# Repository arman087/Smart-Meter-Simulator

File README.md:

# Smart Meter Simulator

Portable lab board that **acts like a Dutch/Belgian DSMR smart meter P1 port**.  
Park it on battery in a building corner, plug in [P1 Ghost](https://github.com/arman087/P1_ghost), and test Ghost Wi‑Fi range without a real meter.

| This board (meter) | P1 Ghost / OSM (reader) |
|--------------------|-------------------------|
| Female RJ12 | Male RJ12 |
| **Supplies** +5 V on pin 1 | Takes +5 V |
| **Senses** Data Request on pin 2 | Drives Request high |
| **Open-collector / opto** Data on pin 5 | Reads Data |

**MCU:** ESP32-C3-MINI-1 (Wi‑Fi on for config / OTA) · **P1 serial:** 115200 8N1 inverted open-drain  
**Telegram store:** microSD · **Build volume:** ~5 boards (JLCPCB)

**Why / how:** **[DESIGN_REPORT.md](DESIGN_REPORT.md)** · **Firmware:** **[FIRMWARE_GUIDE.md](FIRMWARE_GUIDE.md)** · **Pause / next:** **[NEXT_STEPS.md](NEXT_STEPS.md)** · **KiCad:** `my_design/Slimme_meter_Sim/`

---

## Progress (schematic + PCB — Aug 2026)

| Block | Status |
|-------|--------|
| USB-C → bq25185 → TPS61023 → **SYS_5V** | Drawn (`SCH_1_USB_5volt_sch`) |
| **TPS26625** eFuse → `P1_5V`, caps, green power LED, test points, RJ12 | Drawn |
| **SY8088** buck → **VCC_3V3** | Drawn |
| **ESP32-C3-MINI-1** on 3V3; EN RC; GPIO2/8 pull-ups; USB = GPIO18/19 | Drawn |
| RGB on GPIO10; Schottky-fed LED supply | Drawn |
| **6N137S** Data TX (GPIO21 / `ESP32_TX` → pin 5) + Request (`RJ12_pin2` → `ESP32_enable`) | Drawn |
| PCB placement / routing | In progress (saved in KiCad) |
| Assemble first board (stencil + hot air) | See [NEXT_STEPS.md](NEXT_STEPS.md) |
| Optional: Pi as alternate “brain” (own PSU; board keeps P1 power path) | Parked in [NEXT_STEPS.md](NEXT_STEPS.md) |
| microSD, ESD polish | Later |

Sheets: `SCH_1_USB_5volt_sch.kicad_sch` · `SCH_2_power_supplies.kicad_sch`

**Firmware pin polarities / UART invert:** see **[FIRMWARE_GUIDE.md](FIRMWARE_GUIDE.md)** (Request = active **LOW**, Data via OC opto).

---

## Locked power architecture

```
USB-C ──► bq25185 ──► VSYS / V+ (≈3.0–4.5 V) ──► TPS61023 ──► SYS_5V (+5 V)
              │                                      │
           LiPo (2-wire)              ┌──────────────┴──────────────┐
                                      ▼                             ▼
                               SY8088 → 3.3 V              TPS26625 (hiccup)
                                      ▼                             ▼
                                  VCC_3V3                        P1_5V → RJ12 pin1
                                  ESP32 / SD
```

| Net | What it is |
|-----|------------|
| `VSYS` / `V+` | bq25185 system rail — **not** 5 V |
| `SYS_5V` | TPS61023 boost |
| `VCC_3V3` | SY8088 from `SYS_5V` |
| `P1_5V` | TPS26625 out (~250 mA DSMR-like) |

---

## What’s left: Request + Data optos (important)

**Do not** wire ESP32 UART TX (3.3 V push-pull) straight to RJ12 pin 5.

There are **two domains**:

1. **MCU side = 3.3 V** — ESP32 GPIO / UART only talks to the **LED** of each opto.  
2. **P1 side = 5 V** — RJ12 pins 1/2/5 live here (`P1_5V`, Request, Data). Opto **transistor** open-collector sits on this side.

### A) Data Request (pin 2 → GPIO) — “Ghost says start sending”

```
RJ12 pin2 (P1_REQ, ~5 V when active)
    │
    R_LED ──►| opto LED |── GND          ← 5 V / P1 side
                   ║
              opto transistor
                   ║
VCC_3V3 ── Rpu ── collector ──► ESP32 GPIO   ← 3.3 V side
                   emitter ── GND
```

- You **never drive** pin 2 from the MCU.  
- Use a **fast** opto (TLP2361 / 6N137 class — not slow PC817).  
- Firmware: GPIO high/low (document polarity) → start/stop telegram TX.

### B) Data out (GPIO TX → pin 5) — open-collector / opto

```
ESP32 TX (3.3 V) ── R_LED ──►| opto LED |── GND     ← 3.3 V side only
                                  ║
                             opto transistor
                                  ║
RJ12 pin5 (P1_DATA) ── collector     (open collector)
                         emitter ── GND
                         optional: 4.7 kΩ to P1_5V for bench without Ghost
```

- **UART pin stays at 3.3 V** — it only lights the opto LED.  
- **Pin 5 is the 5 V / OC world** — transistor pulls Data low; Ghost’s pull-up (or your 4.7 kΩ) makes high.  
- 115200 baud → **fast** opto.  
- Detail notes: `circuits/07_data_request_sense/` · `circuits/08_open_collector_data/`

---

## Subcircuits

| Folder | Status |
|--------|--------|
| [circuits/01_usb_c_input](circuits/01_usb_c_input) | USB data → ESP32 |
| [circuits/02_battery_and_power_mux](circuits/02_battery_and_power_mux) | bq25185 + TPS61023 |
| [circuits/03_5v_to_3v3](circuits/03_5v_to_3v3) | **SY8088** → 3.3 V |
| [circuits/04_p1_5v_current_limit](circuits/04_p1_5v_current_limit) | **TPS26625** + RILIM calc |
| [circuits/05_esp32_c3_mini](circuits/05_esp32_c3_mini) | ESP32-C3-MINI-1 |
| [circuits/06_rj12_connector](circuits/06_rj12_connector) | RJ12 meter jack |
| [circuits/07_data_request_sense](circuits/07_data_request_sense) | Pin 2 → opto → GPIO **← do next** |
| [circuits/08_open_collector_data](circuits/08_open_collector_data) | TX → opto OC → pin 5 **← do next** |
| [circuits/09_esd_protection](circuits/09_esd_protection) | USB + RJ12 ESD |
| [circuits/10_ui_led_button](circuits/10_ui_led_button) | RGB + optional button |
| [circuits/11_optional_isolation](circuits/11_optional_isolation) | Optos + optional iso DC-DC |
| [circuits/12_microsd](circuits/12_microsd) | microSD |

## References

- [P1 Companion Standard 5.0.2](https://www.netbeheernederland.nl/sites/default/files/2024-02/dsmr_5.0.2_p1_companion_standard.pdf)
- [TI slvaf94 — TPS2662](https://www.ti.com/lit/pdf/slvaf94)
- [TI bq25185](https://www.ti.com/product/BQ25185) · [TI TPS61023](https://www.ti.com/product/TPS61023)
- [arman087/P1_ghost](https://github.com/arman087/P1_ghost)

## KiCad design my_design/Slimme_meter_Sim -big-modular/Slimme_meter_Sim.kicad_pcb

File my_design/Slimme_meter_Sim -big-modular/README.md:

# Slimme meter Sim — big modular (hand-build)

**Active path:** this folder only.  
Parent `DESIGN_GUIDE.md` / root README are **not** source of truth for this build.

Portable **DSMR P1 meter-side** simulator: battery in a corner, Ghost on RJ12, Wi‑Fi range tests without a real meter.

---

## Locked modular plan (return-to-work)

| Piece | How it is built |
|-------|-----------------|
| **ESP32-S3** | **Module:** Espressif **ESP32-S3-DevKitC-1-N32R16V** (**WROOM-2**, 32 MB flash + 16 MB PSRAM) — same 2×22 headers, onboard 5 V→3.3 V LDO. Alt: **N16R8V** |
| **USB-C (charge)** | **Breakout module** → soldered/wired to main PCB (not a tiny USB-C footprint on your board) |
| **microSD** | **Breakout module** → SPI wires to DevKit (not onboard SD slot) |
| **Charger IC** | On **main PCB** — hand-solder (bigger package preferred) |
| **5 V boost** | On **main PCB** — hand-solder (**bigger package** preferred) |
| **eFuse / current limit** | On **main PCB** — **both** TPS2662 + TPS2553, select with jumper / 0 Ω |
| **Optos + RJ12** | On **main PCB** — **6N137 DIP-8** ×2, RJ12, ESD |

**Not on main PCB:** DevKit MCU, USB-C receptacle soldering challenge, SD cage soldering challenge.

---

## Power rules (do not loop-charge)

```
Main USB-C breakout ──► charger ──► LiPo / VSYS ──► boost ──► 5V_SYS
                                                              ├── eFuse → RJ12 pin 1
                                                              └── [SW] ──|>|──► DevKit "5V"

DevKit USB ──► program / first flash ONLY
               NEVER wired into the charger
```

| Rule | Why |
|------|-----|
| **Only main USB-C charges** | Avoids boost → DevKit 5V → charger fake-charge loop |
| **`[SW]` between 5V_SYS and DevKit `5V`** | Open while programming on DevKit USB; closed for normal run |
| **Diode on 5V_SYS → DevKit** | Extra reverse protection when switch is closed and habits slip |
| **After first flash** | Prefer Wi‑Fi / OTA; leave DevKit USB unused |

### Switch habit

| Mode | Switch `5V_SYS → DevKit` | USB |
|------|--------------------------|-----|
| First flash / recovery | **OPEN** | DevKit USB only |
| Field / normal | **CLOSED** | Main USB-C charge (or battery); talk over Wi‑Fi |

---

## Hand-solder focus (your three ICs)

1. **Charger** (e.g. path like bq25185-class / Adafruit #6106 as reference)  
2. **Boost** — bigger package / module-friendly footprint  
3. **eFuse** — see decision below  

Everything else painful (USB-C, SD) = **bought breakouts**.

---

## eFuse: populate **both**, select one

Put **TPS2662** (foldback / rich) **and** **TPS2553** (bigger / easy) on the same PCB. Only one path to RJ12 pin 1 is live.

```
5V_SYS ──┬──► TPS2662 ──┐
         │              ├── [jumper / 0 Ω / SW] ──► RJ12 pin1
         └──► TPS2553 ──┘
```

| Select | When |
|--------|------|
| **TPS2662 path** | Reflow succeeded — use the “amazing” part |
| **TPS2553 path** | Tiny IC bridged / dead / skipped — still ship the board |

**Select hardware (pick one style in KiCad):**
- Two **0 Ω** positions (fit only one), or  
- **2.54 mm jumper** ( clearest for bring-up), or  
- SPDT switch (handy, slightly more drop/noise — fine for P1)

**Do not** leave both outputs paralleled with no select — fight / odd current paths.

Try the tiny IC with paste + hot plate; if it fails, open that path and close TPS2553. No board respin required.

---

## Tomorrow checklist

1. KiCad: power sheet — charger → VSYS → boost → `5V_SYS`  
2. KiCad: DevKit header footprint + **SW + diode** to DevKit `5V`  
3. KiCad: USB-C **breakout** connector footprint / pin header (VBUS, GND, maybe CC if needed)  
4. KiCad: SD **breakout** header (SPI + 3V3 + GND)  
5. KiCad: **both** eFuse footprints + **select jumper/0 Ω** → RJ12  
6. KiCad: 6N137 ×2 + ESD  

Detail: [ARCHITECTURE.md](ARCHITECTURE.md) · [PARTS_CHECKLIST.md](PARTS_CHECKLIST.md)

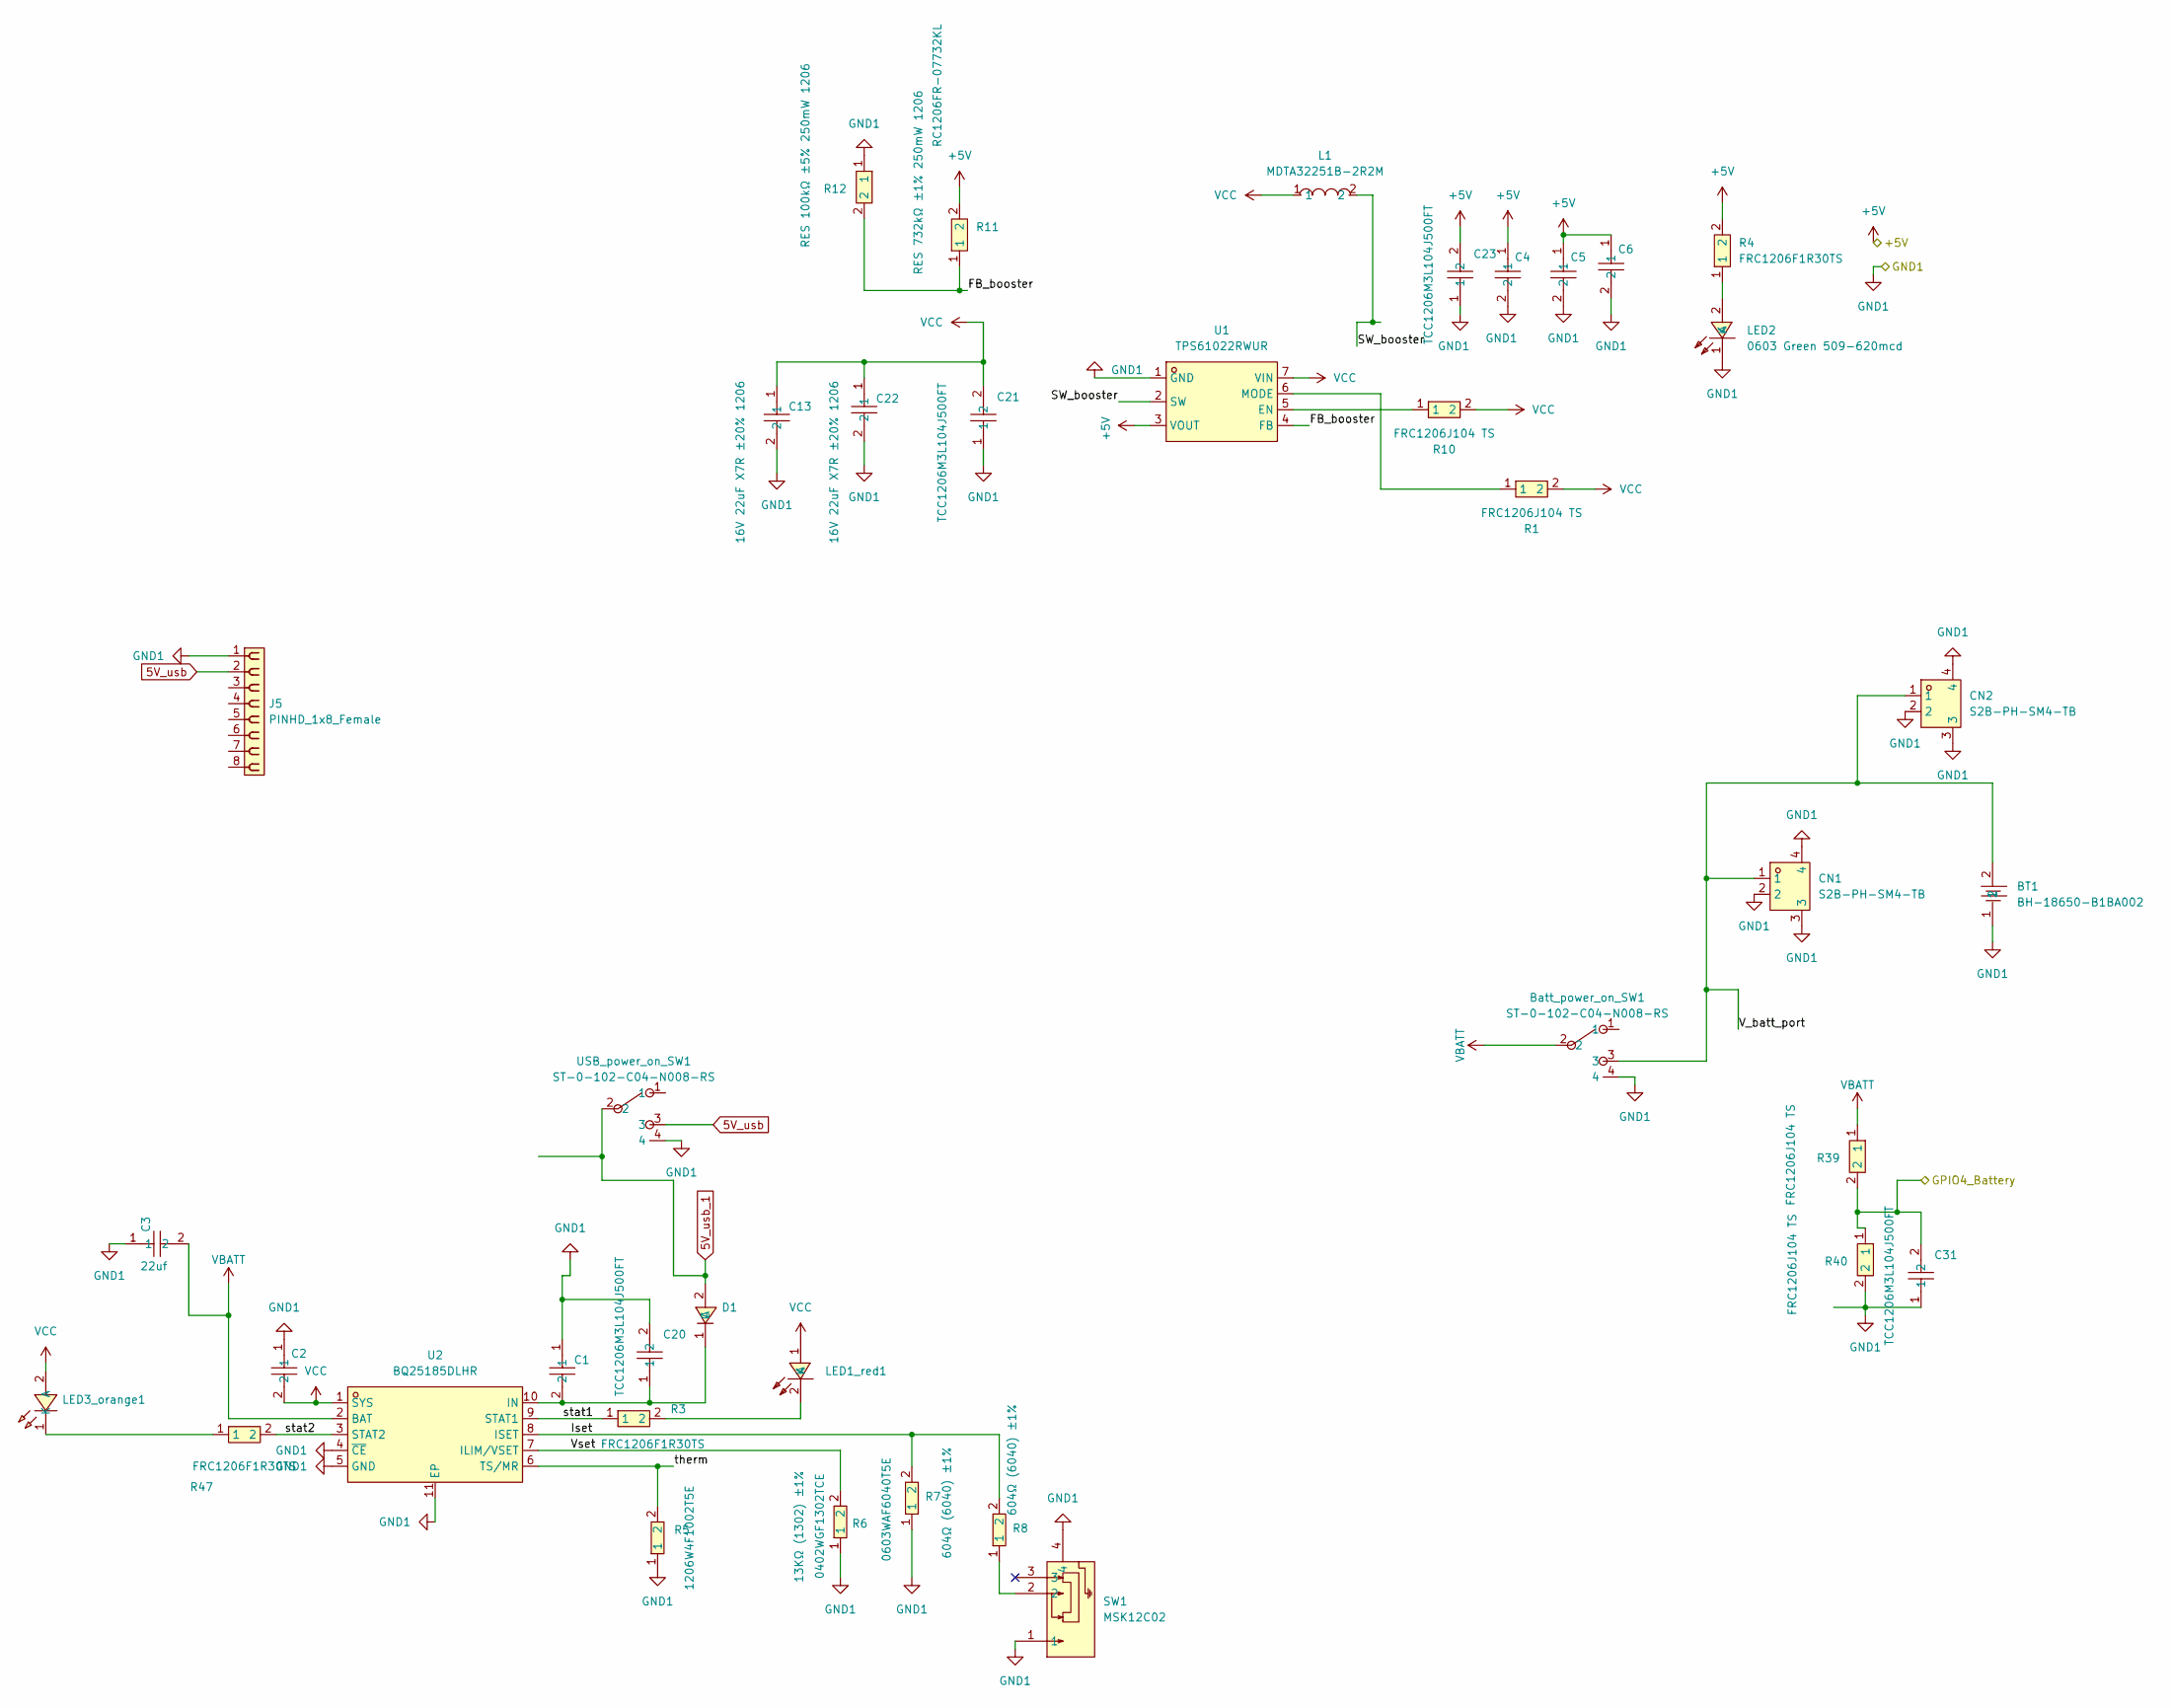
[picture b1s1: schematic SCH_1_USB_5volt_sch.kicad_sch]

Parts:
BT1: BH-18650-B1BA002; BATTERY-SMD_18650-1S-L77.1-W20.7-1; MPN BH-18650-B1BA002; LCSC Part C2988620
Batt_power_on_SW1: ST-0-102-C04-N008-RS; SW-TH_ST-0-102-C04-N008-RS; MPN ST-0-102-C04-N008-RS; LCSC Part C1788491
C1, C2, C3, C4, C5, C6, C13, C22: FS31X226M160EPG; C1206; MPN FS31X226M160EPG; LCSC Part C3036083
C20, C21, C23, C31: TCC1206M3L104J500FT; C1206; MPN TCC1206M3L104J500FT; LCSC Part C359189
CN1, CN2: S2B-PH-SM4-TB; CONN-SMD_P2.00_S2B-PH-SM4-TB-LF-SN; MPN S2B-PH-SM4-TB(LF)(SN); LCSC Part C295747
D1: NSR0320MW2T1G; SOD-323_L1.8-W1.3-LS2.5-RD; MPN NSR0320MW2T1G; LCSC Part C48192
J5: PINHD_1x8_Female; PinSocket_1x08_P2.54mm_Vertical
L1: MDTA32251B-2R2M; IND-SMD_L3.2-W2.5-BRL3225T100M; MPN MDTA32251B-2R2M; LCSC Part C22388372
LED1_red1: KT-0603R; LED-SMD_L1.6-W0.8-R-RD; MPN KT-0603R; LCSC Part C2286
LED2: 0603 Green 509-620mcd; LED0603-RD; MPN KT-0603G; LCSC Part C12624
LED3_orange1: KT-0603O; LED0603-RD; MPN KT-0603O; LCSC Part C111340
R1, R10, R12, R39, R40: FRC1206J104 TS; R1206; MPN FRC1206J104 TS; LCSC Part C2907421
R3, R4, R47: FRC1206F1R30TS; R1206; MPN FRC1206F1R30TS; LCSC Part C2907365
R5: 1206W4F1002T5E; R1206; MPN 1206W4F1002T5E; LCSC Part C17902
R6: 0402WGF1302TCE; R0402; MPN 0402WGF1302TCE; LCSC Part C25754
R7, R8: 0603WAF6040T5E; R0603; MPN 0603WAF6040T5E; LCSC Part C32183
R11: RC1206FR-07732KL; R1206; MPN RC1206FR-07732KL; LCSC Part C488960
SW1: MSK12C02; SW-TH_MSK12C02; MPN MSK12C02; LCSC Part C431540
U1: TPS61022RWUR; VQFN-7_L2.0-W2.0-P0.55-TL_RWU; MPN TPS61022RWUR; LCSC Part C915088
U2: BQ25185DLHR; WSON-10_L2.2-W2.0-P0.40-BL-EP_TI_DLH0010A; MPN BQ25185DLHR; LCSC Part C19725033
USB_power_on_SW1: ST-0-102-C04-N008-RS; SW-TH_ST-0-102-C04-N008-RS; MPN ST-0-102-C04-N008-RS; LCSC Part C1788491

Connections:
5V_usb: J5.2, USB_power_on_SW1.3
5V_usb_1: D1.2 (A), USB_power_on_SW1.2
+5V: C4.1, C5.1, C6.1, C23.2, R4.2, R11.2, U1.3 (VOUT); also elsewhere on the board
/SCH_1_USB_5volt/GPIO4_Battery: C31.2, R39.2, R40.1; also elsewhere on the board
/SCH_1_USB_5volt/Iset: R7.2, R8.2, U2.8 (ISET)
/SCH_1_USB_5volt/V_batt_port: BT1.2, Batt_power_on_SW1.3, CN1.1, CN2.1
/SCH_1_USB_5volt/Vset: R6.2, U2.7 (ILIM/VSET)
/SCH_1_USB_5volt/stat1: R3.1, U2.9 (STAT1)
/SCH_1_USB_5volt/stat2: R47.2, U2.3 (STAT2)
/SCH_1_USB_5volt/therm: R5.2, U2.6 (TS/MR)
GND: BT1.1, Batt_power_on_SW1.4, C1.1, C2.1, C3.1, C4.2, C5.2, C6.2, C13.2, C20.2, C21.1, C22.2, C23.1, C31.1, CN1.2, CN1.3, CN1.4, CN2.2, CN2.3, CN2.4, J5.1, LED2.1 (K), R5.1, R6.1, R7.1, R12.1, R40.2, SW1.1, SW1.4, U1.1 (GND), U2.4 (~CE), U2.5 (GND), U2.11 (EP), USB_power_on_SW1.4; also elsewhere on the board
unnamed: C1.2, C20.1, D1.1 (C), U2.10 (IN)
unnamed: LED1_red1.2 (K), R3.2
unnamed: LED2.2 (A), R4.1
unnamed: LED3_orange1.1 (K), R47.1
unnamed: R1.1, U1.6 (MODE)
unnamed: R8.1, SW1.2
unnamed 34: R10.1, U1.5 (EN); also elsewhere on the board
unnamed 35: R11.1, R12.2, U1.4 (FB); also elsewhere on the board
unnamed 36: L1.2, U1.2 (SW); also elsewhere on the board
VBATT: Batt_power_on_SW1.2, C3.2, R39.1, U2.2 (BAT)
VCC: C2.2, C13.1, C21.2, C22.1, L1.1, LED1_red1.1 (A), LED3_orange1.2 (A), R1.2, R10.2, U1.7 (VIN), U2.1 (SYS); also elsewhere on the board

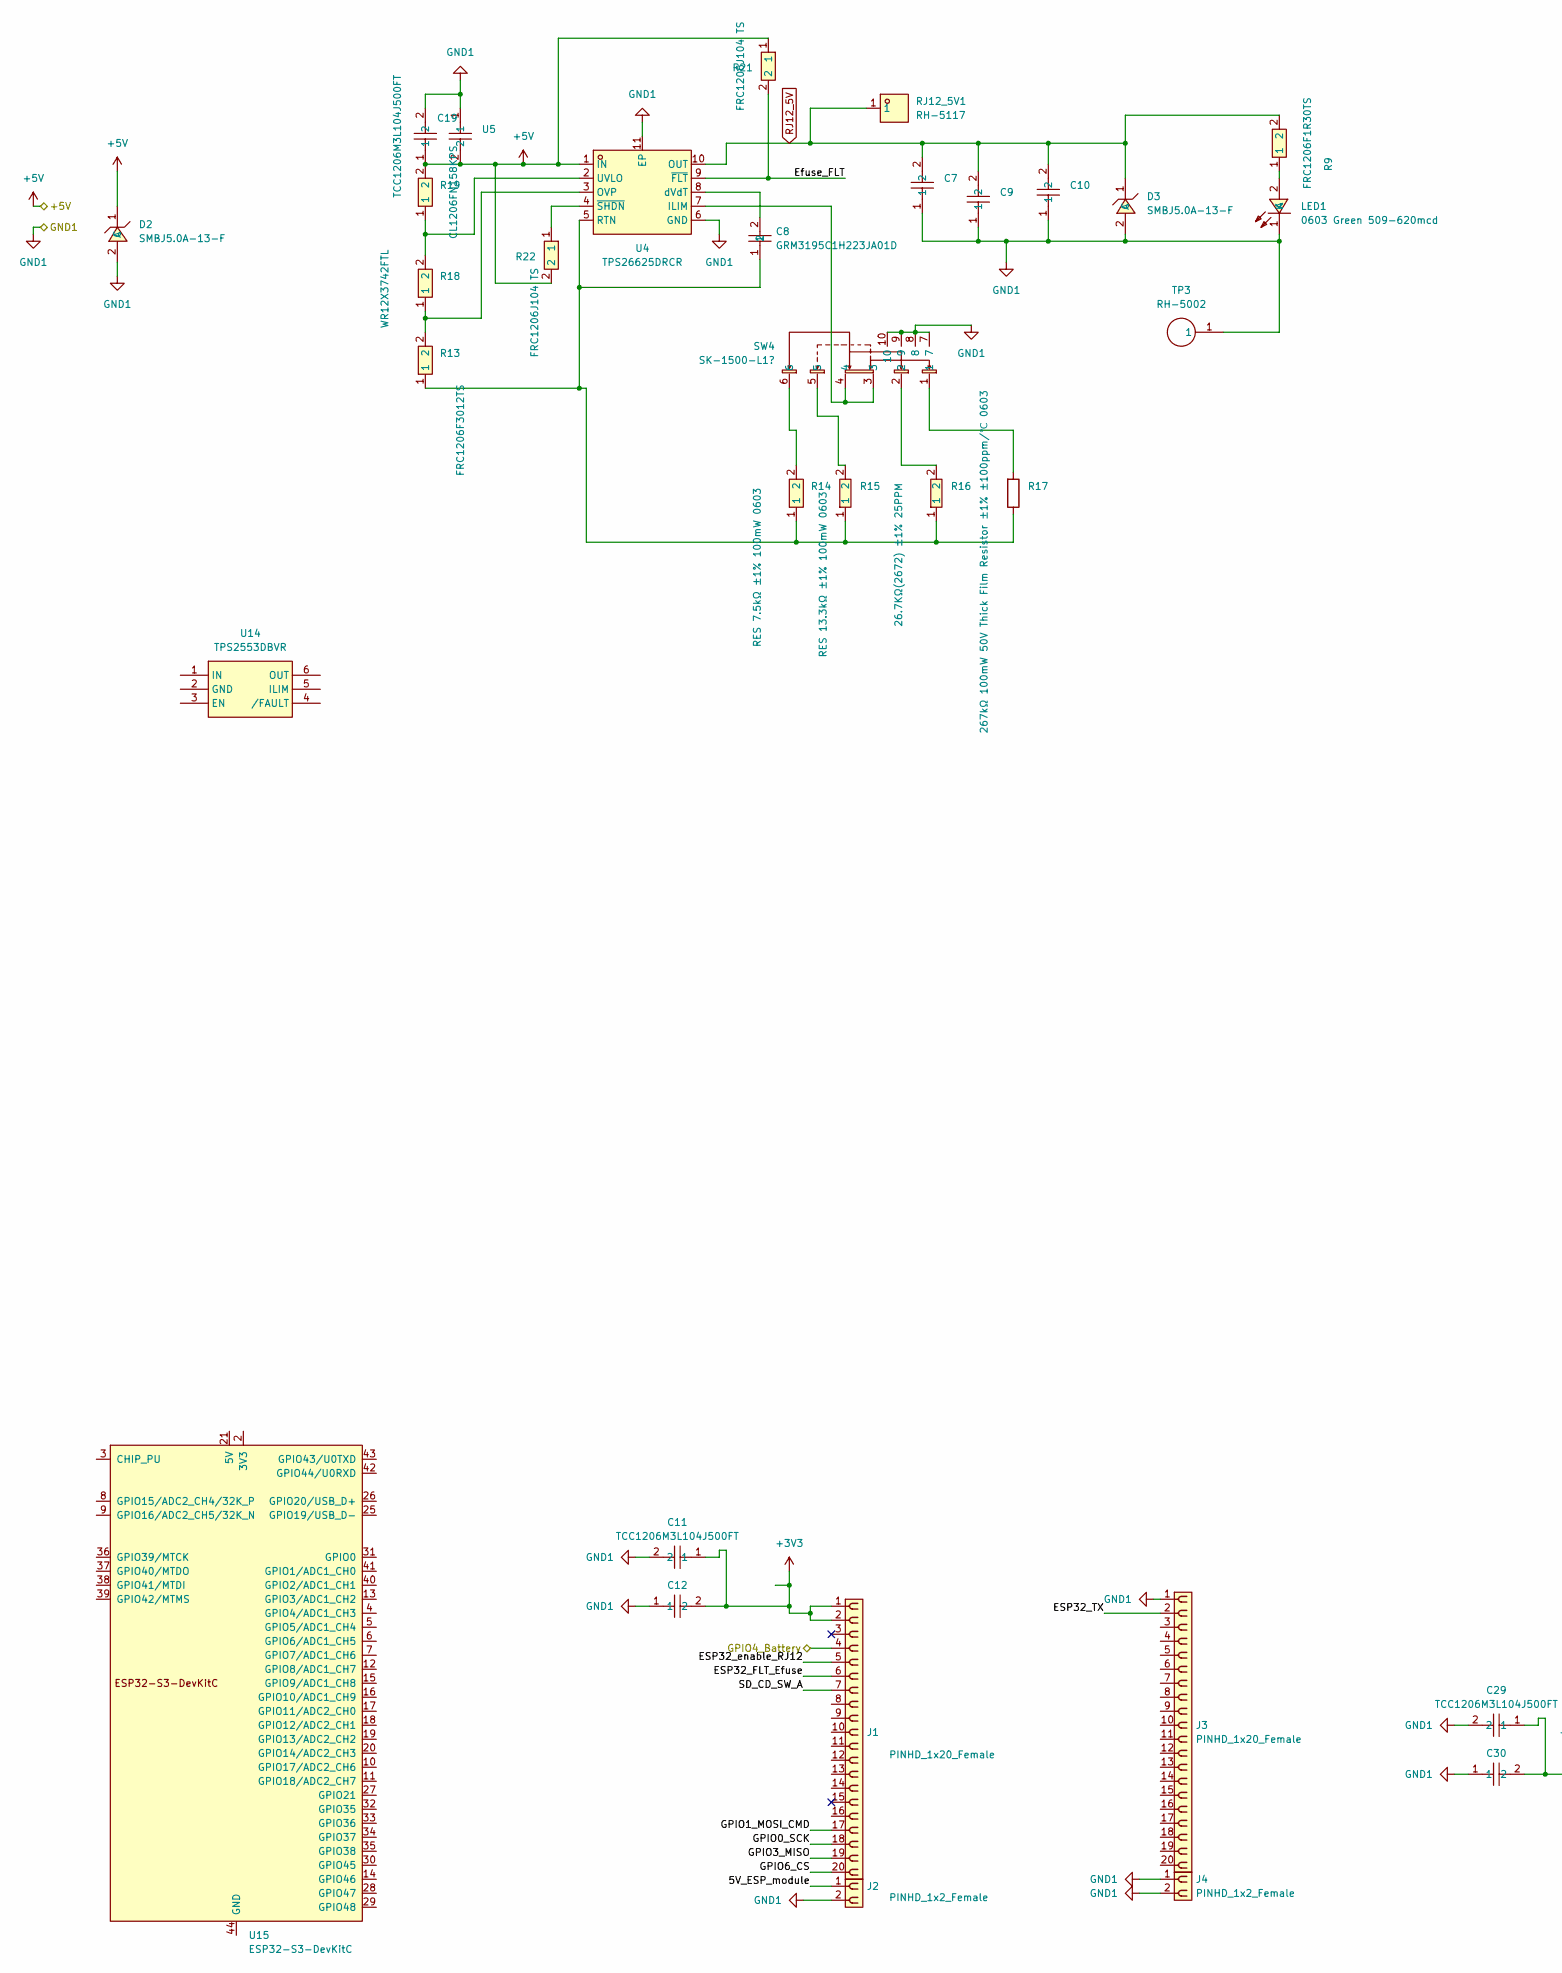
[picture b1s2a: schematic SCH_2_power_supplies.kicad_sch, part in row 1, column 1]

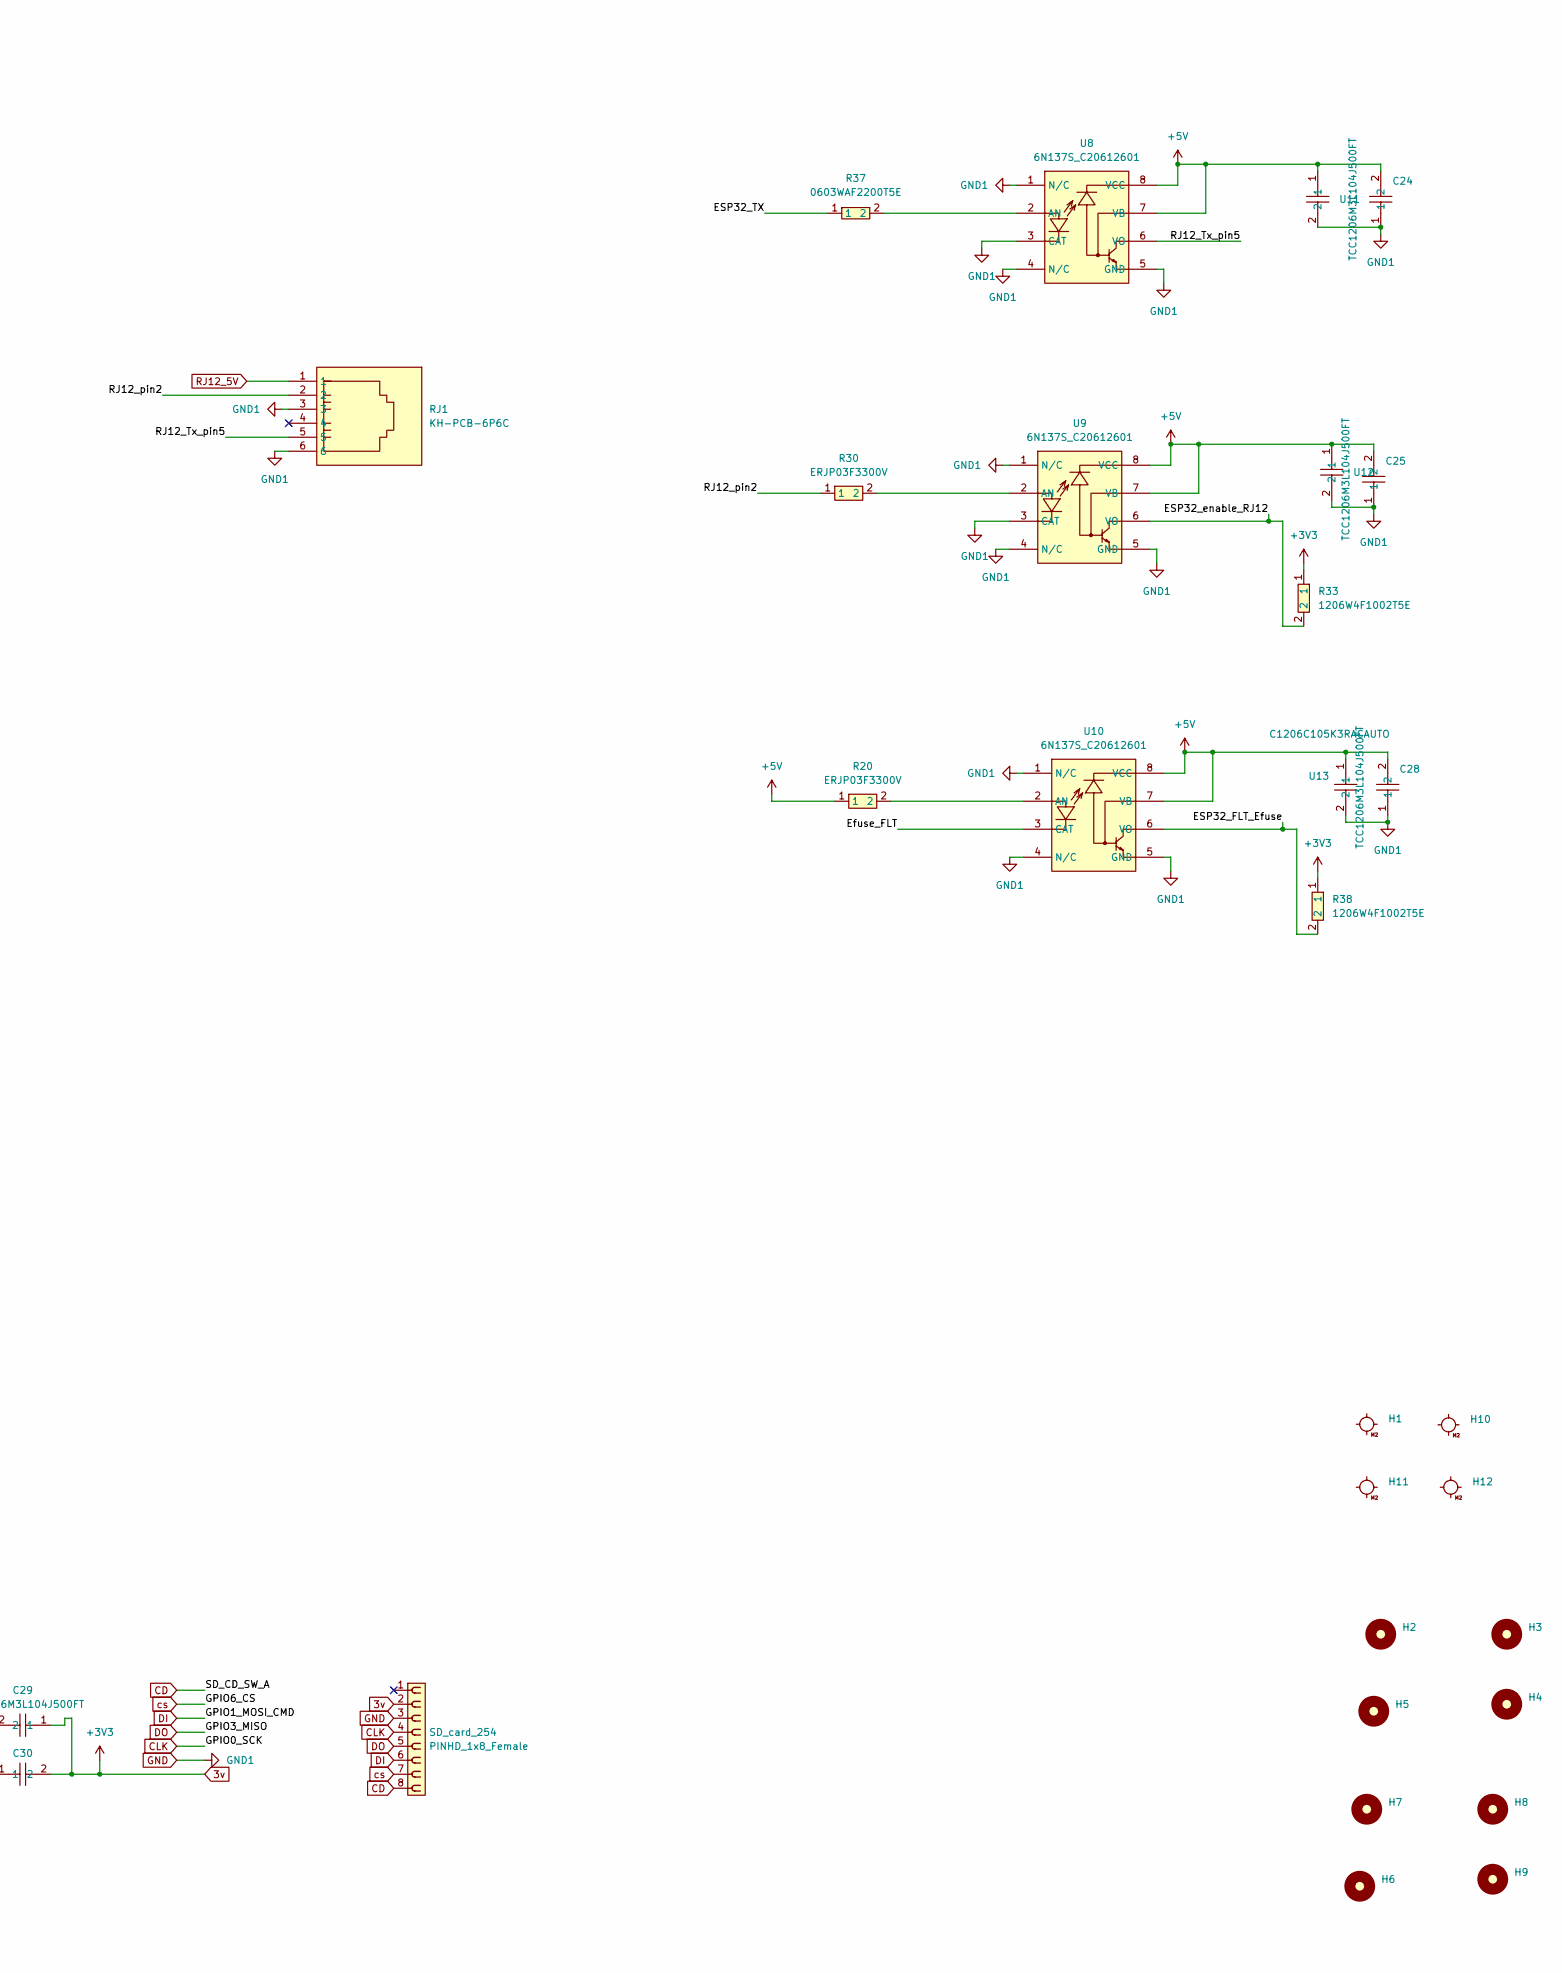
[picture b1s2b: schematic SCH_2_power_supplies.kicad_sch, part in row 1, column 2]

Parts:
C7: C1206C225K3RACTU; C1206; MPN C1206C225K3RACTU; LCSC Part C2167942
C8: GRM3195C1H223JA01D; C1206; MPN GRM3195C1H223JA01D; LCSC Part C97929
C9, C10: GRM32ER71J106KA12L_C437568; C1210; MPN GRM32ER71J106KA12L; LCSC Part C437568
C11, C19, C24, C25, C28, C29: TCC1206M3L104J500FT; C1206; MPN TCC1206M3L104J500FT; LCSC Part C359189
C12, C30: FS31X226M160EPG; C1206; MPN FS31X226M160EPG; LCSC Part C3036083
D2, D3: SMBJ5.0A-13-F; SMB_L4.6-W3.6-LS5.3-RD; MPN SMBJ5.0A-13-F; LCSC Part C110528
H1, H10, H11, H12: MountingHole_M2
H2, H3, H4, H5, H6, H7, H8, H9: MountingHole_3.2mm_M3
J1, J3: PINHD_1x20_Female; PinSocket_1x20_P2.54mm_Vertical
J2, J4: PINHD_1x2_Female; PinSocket_1x02_P2.54mm_Vertical
LED1: 0603 Green 509-620mcd; LED0603-RD; MPN KT-0603G; LCSC Part C12624
R9: FRC1206F1R30TS; R1206; MPN FRC1206F1R30TS; LCSC Part C2907365
R13: FRC1206F3012TS; R1206; MPN FRC1206F3012TS; LCSC Part C48533691
R14: CRCW06037K50FKEA; R0603; MPN CRCW06037K50FKEA; LCSC Part C844808
R15: RS-03K1332FT; R0603; MPN RS-03K1332FT; LCSC Part C321713
R16: AR03FTC2672; R0603; MPN AR03FTC2672; LCSC Part C234417
R17: HRC0603F2673ENTN; R_0603_1608Metric; MPN HRC0603F2673ENTN; LCSC Part C55098397
R18: WR12X3742FTL; R1206; MPN WR12X3742FTL; LCSC Part C908492
R19: CL1206FN158KPS; R1206; MPN CL1206FN158KPS; LCSC Part C53283992
R20, R30: ERJP03F3300V; R0603; MPN ERJP03F3300V; LCSC Part C427299
R21, R22: FRC1206J104 TS; R1206; MPN FRC1206J104 TS; LCSC Part C2907421
R33, R38: 1206W4F1002T5E; R1206; MPN 1206W4F1002T5E; LCSC Part C17902
R37: 0603WAF2200T5E; R0603; MPN 0603WAF2200T5E; LCSC Part C22962
RJ1: KH-PCB-6P6C; RJ45-TH_KH-PCB-6P6C; MPN KH-PCB-6P6C; LCSC Part C2683354
RJ12_5V1: RH-5117; TESTPOINT-TH_BD3.2-D1.6; MPN RH-5117; LCSC Part C5199807
SD_card_254: PINHD_1x8_Female; PinSocket_1x08_P2.54mm_Vertical
SW4: SK-1500-L1?; SW-SMD_6P-P1.50_L2.7-W11.2; MPN SK-1500-L1; LCSC Part C319025
TP3: RH-5002; TESTPOINT-TH_BD2.5-D1.2_RH-5002; MPN RH-5002; LCSC Part C5199802
U4: TPS26625DRCR; VSON-10_L3.0-W3.0-P0.50-TL-EP-1; MPN TPS26625DRCR; LCSC Part C2862873
U5, U11, U12, U13: C1206C105K3RACAUTO; C1206; MPN C1206C105K3RACAUTO; LCSC Part C2167173
U8, U9, U10: 6N137S_C20612601; SOP-8_L9.7-W6.5-P2.54-LS10.3-BL; MPN 6N137S; LCSC Part C20612601
U14: TPS2553DBVR; SOT-23-6_L2.9-W1.6-P0.95-LS2.8-BR; MPN TPS2553DBVR; LCSC Part C55266
U15: ESP32-S3-DevKitC

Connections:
3v: C11.1, C12.2, C29.1, C30.2, J1.1, J1.2, R33.1, R38.1, SD_card_254.2
+5V: C19.1, C24.2, C25.2, C28.2, D2.1 (C), R19.2, R20.1, R21.1, R22.2, U4.1 (IN), U5.2, U8.7 (VB), U8.8 (VCC), U9.7 (VB), U9.8 (VCC), U10.7 (VB), U10.8 (VCC), U11.1, U12.1, U13.1; also elsewhere on the board
/SCH_1_USB_5volt/GPIO4_Battery: J1.4; also elsewhere on the board
/SCH_2_power_supplies/5V_ESP_module: J2.1
/SCH_2_power_supplies/ESP32_FLT_Efuse: J1.6, R38.2, U10.6 (VO)
/SCH_2_power_supplies/ESP32_TX: J3.2, R37.1
/SCH_2_power_supplies/ESP32_enable_RJ12: J1.5, R33.2, U9.6 (VO)
/SCH_2_power_supplies/Efuse_FLT: R21.2, U4.9 (~FLT), U10.3 (CAT)
/SCH_2_power_supplies/RJ12_Tx_pin5: RJ1.5, U8.6 (VO)
/SCH_2_power_supplies/RJ12_pin2: R30.1, RJ1.2
CD: J1.7, SD_card_254.8
CLK: J1.18, SD_card_254.4
DI: J1.17, SD_card_254.6
DO: J1.19, SD_card_254.5
GND: C7.1, C9.1, C10.1, C11.2, C12.1, C19.2, C24.1, C25.1, C28.1, C29.2, C30.1, D2.2 (A), D3.2 (A), J2.2, J3.1, J4.1, J4.2, LED1.1 (K), RJ1.3, RJ1.6, SD_card_254.3, SW4.7, SW4.8, SW4.9, SW4.10, TP3.1, U4.6 (GND), U4.11 (EP), U5.1, U8.1 (N/C), U8.3 (CAT), U8.4 (N/C), U8.5 (GND), U9.1 (N/C), U9.3 (CAT), U9.4 (N/C), U9.5 (GND), U10.1 (N/C), U10.4 (N/C), U10.5 (GND), U11.2, U12.2, U13.2; also elsewhere on the board
unnamed: LED1.2 (A), R9.1
unnamed: R14.2, SW4.6
unnamed: R15.2, SW4.5
unnamed: R16.2, SW4.2
unnamed: R17.1, SW4.1
unnamed: SW4.3, SW4.4, U4.7 (ILIM)
unnamed: R13.2, R18.1, U4.3 (OVP)
unnamed: C8.1, R13.1, R14.1, R15.1, R16.1, R17.2, U4.5 (RTN)
unnamed: R18.2, R19.1, U4.2 (UVLO)
unnamed: C8.2, U4.8 (dVdT)
unnamed: R22.1, U4.4 (~SHDN)
unnamed: R37.2, U8.2 (AN)
unnamed: R30.2, U9.2 (AN)
unnamed: R20.2, U10.2 (AN)
unnamed: U15.1 (3V3), U15.2 (3V3)
unnamed: U15.22 (GND), U15.23 (GND), U15.24 (GND), U15.44 (GND)
RJ12_5V: C7.2, C9.2, C10.2, D3.1 (C), R9.2, RJ1.1, RJ12_5V1.1, U4.10 (OUT)
cs: J1.20, SD_card_254.7

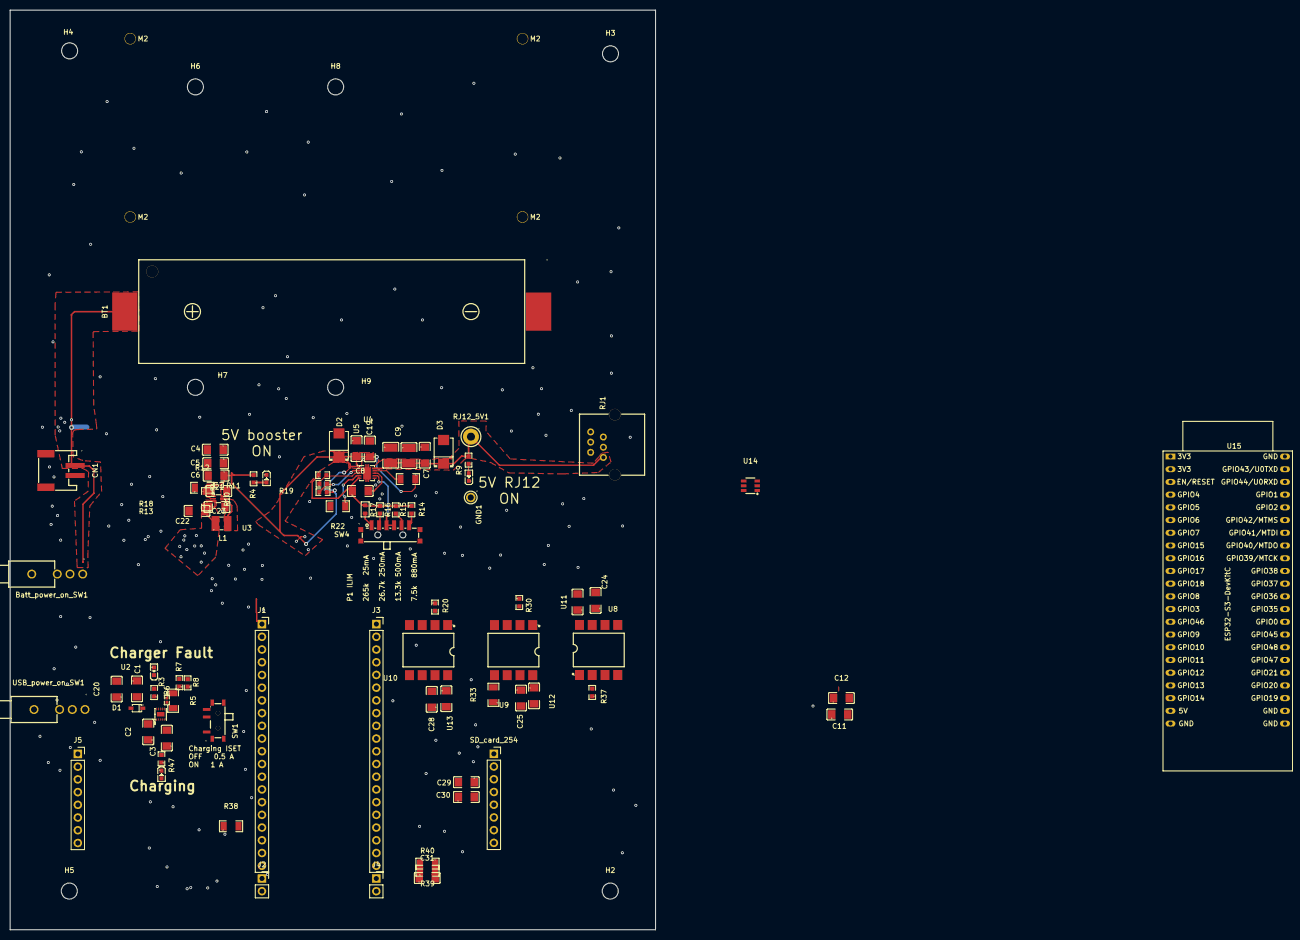
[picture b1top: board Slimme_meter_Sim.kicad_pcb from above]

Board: 2 copper layers, 128.9 x 183.6 mm, 98 parts (1 on the bottom side), 50 nets.

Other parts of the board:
U3: TPS61023DRLR; SOT-563_L1.6-W1.2-P0.50-LS1.6-BR

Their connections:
+5V: U3.6 (VOUT); also elsewhere on the board
GND: U3.4 (GND); also elsewhere on the board
unnamed 34: U3.2 (EN); also elsewhere on the board
unnamed 35: U3.1 (FB); also elsewhere on the board
unnamed 36: U3.5 (SW); also elsewhere on the board
VCC: U3.3 (VIN); also elsewhere on the board

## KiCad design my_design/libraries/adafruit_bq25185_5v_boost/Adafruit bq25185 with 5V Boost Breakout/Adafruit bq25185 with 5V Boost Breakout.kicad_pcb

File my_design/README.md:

# my_design

Working KiCad for the Smart Meter Simulator:

```
my_design/
  Slimme_meter_Sim/          ← product project (start here)
    SCH_1_USB_5volt_sch…     USB-C → bq25185 → TPS61023 → SYS_5V
```

## Power nets

```
USB-C → bq25185 → V+ / VSYS (3.0–4.5 V) → TPS61023 → +5V (SYS_5V)
```

- **bq25185** system rail = `VSYS` (schematic `V+`) — **not** 5 V  
- **TPS61023** is **required** — do not feed P1 or the 3.3 V regulator from `V+` alone  

## Docs

- [DESIGN_REPORT.md](../DESIGN_REPORT.md) — why / how so far  
- [DESIGN_GUIDE.md](../DESIGN_GUIDE.md) — architecture checklist  
- [PARTS_CHECKLIST.md](../PARTS_CHECKLIST.md)  

## Silicon refs

- https://www.ti.com/product/BQ25185  
- https://www.ti.com/product/TPS61023  
- https://www.ti.com/lit/pdf/slvaf94 (P1 foldback / TPS2662)

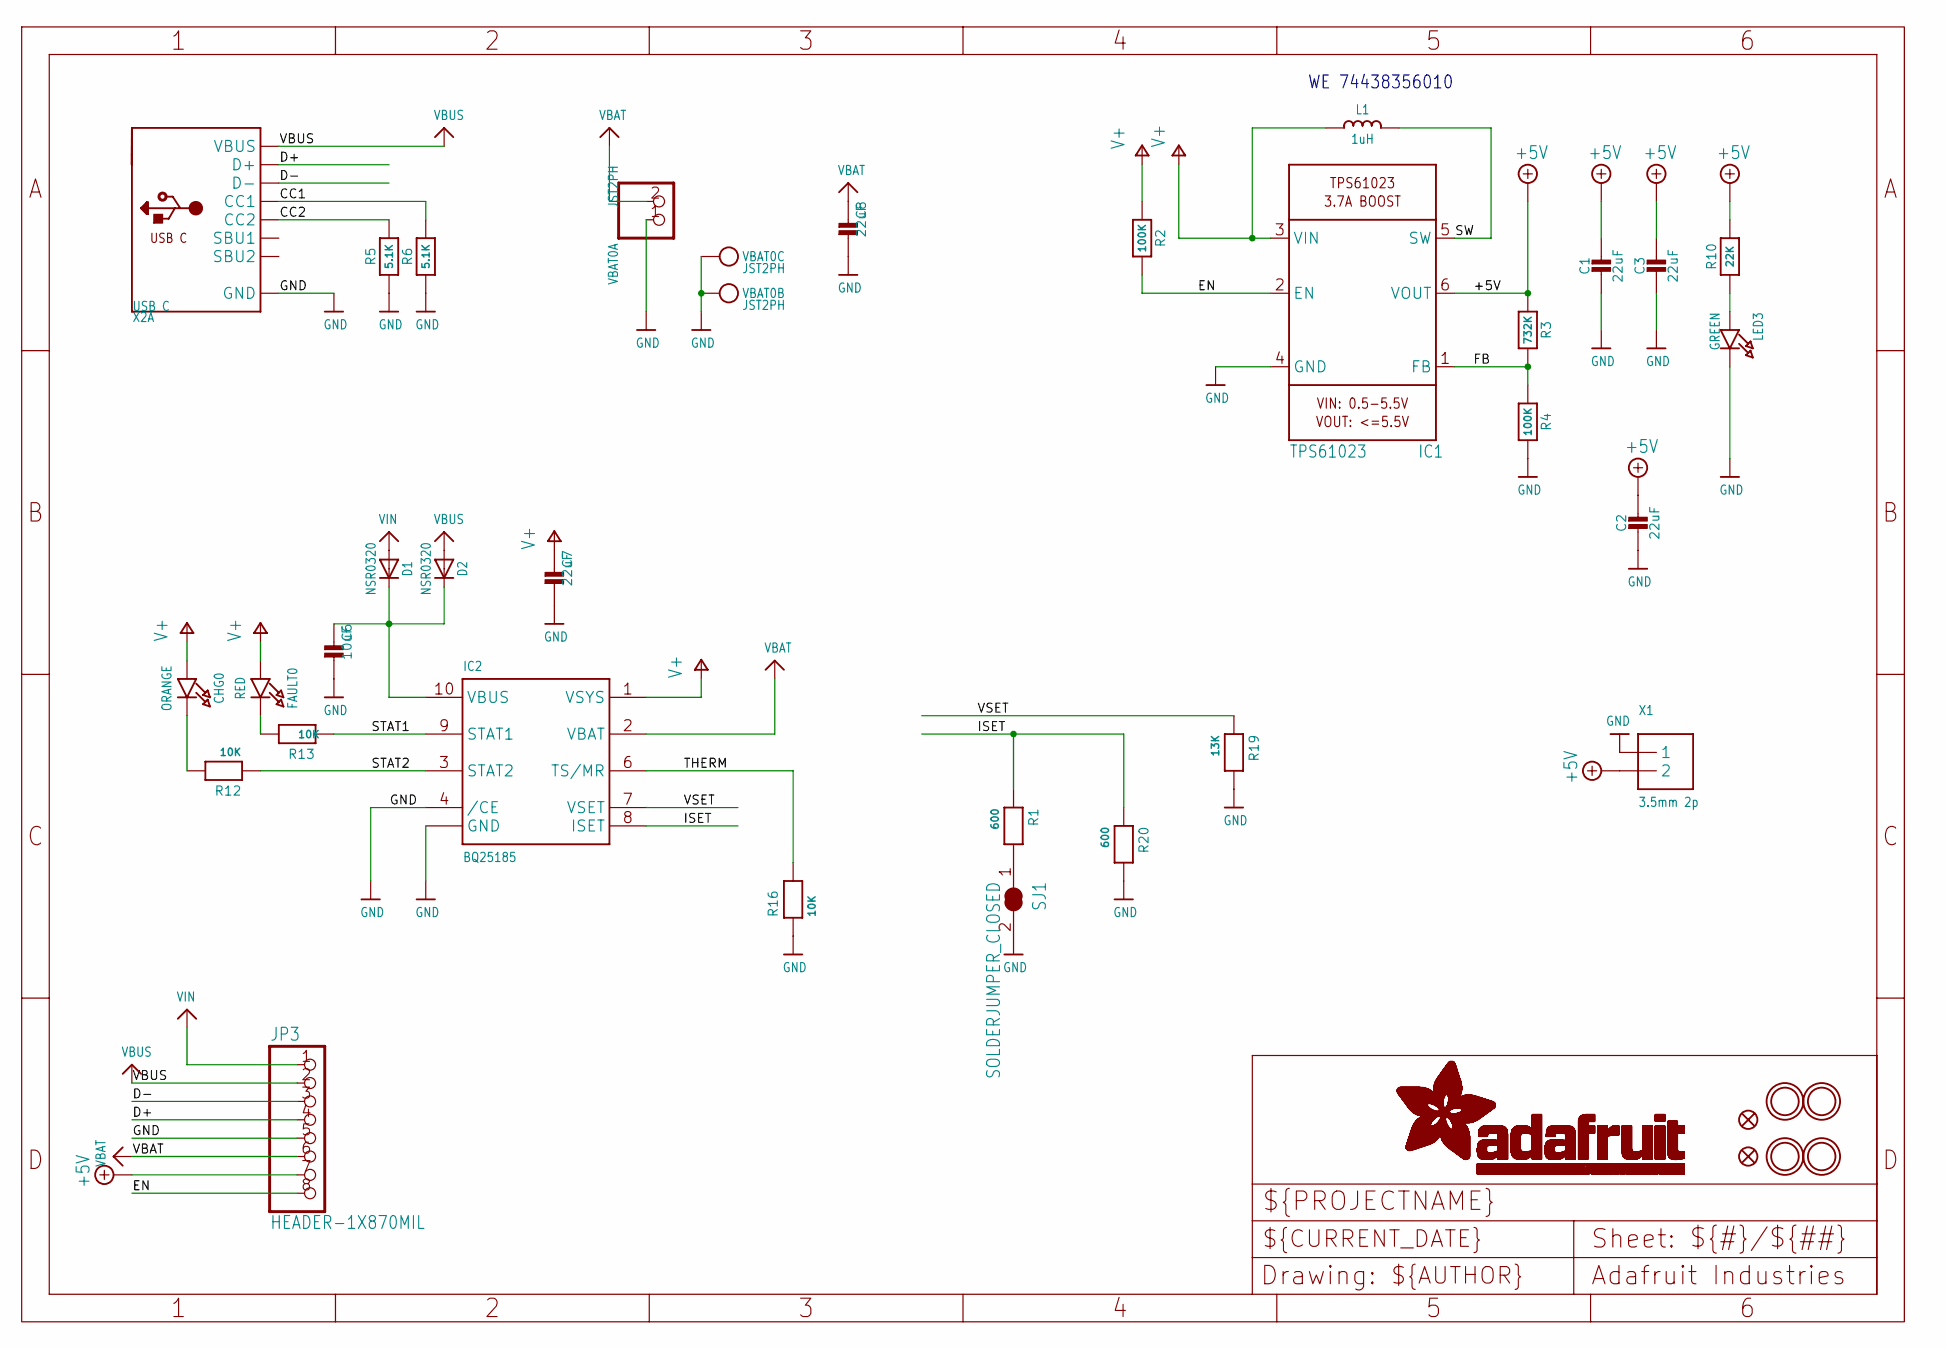
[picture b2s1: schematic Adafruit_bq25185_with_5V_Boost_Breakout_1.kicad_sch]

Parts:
C1, C2, C3, C7, C8: 22uF; 0805-NO
C6: 10uF; 0805-NO
CHG0: ORANGE; CHIPLED_0603_NOOUTLINE
D1, D2: NSR0320; SOD-323_MINI
FAULT0: RED; CHIPLED_0603_NOOUTLINE
FID1, FID2: FIDUCIAL_0.5MM
IC1: TPS61023; SOT563
IC2: BQ25185; WSON10
JP3: HEADER-1X870MIL; 1X08_ROUND_70
L1: 1uH; INDUCTOR_5045_SMALLTABS
LED3: GREEN; CHIPLED_0603_NOOUTLINE
R1, R20: 600; _0402NO
R2, R4: 100K; _0402NO
R3: 732K; _0402NO
R5, R6: 5.1K; _0402NO
R10: 22K; _0402NO
R12, R13, R16: 10K; _0402NO
R19: 13K; _0402NO
SJ1: SOLDERJUMPER_CLOSED; SOLDERJUMPER_CLOSEDWIRE
U$9, U$10, U$11, U$12: MOUNTINGHOLE2.5; MOUNTINGHOLE_2.5_PLATED
VBAT0: JST2PH; JSTPH2_BATT
X1: 3.5mm 2p; TERMBLOCK_1X2-3.5MM
X2: USB C; USB_C_CUSB31-CFM2AX-01-X

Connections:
+5V: C1.1, C2.1, C3.1, IC1.6 (VOUT), JP3.7, R3.1, R10.2, X1.2
CC1: R6.2, X2.A5 (CC1)
CC2: R5.2, X2.B5 (CC2)
D+: JP3.4, X2.A6 (D+), X2.B6 (D+)
D-: JP3.3, X2.A7 (D-), X2.B7 (D-)
EN: IC1.2 (EN), JP3.8, R2.2
FB: IC1.1 (FB), R3.2, R4.1
GND: C1.2, C2.2, C3.2, C6.2, C7.2, C8.2, IC1.4 (GND), IC2.4 (/CE), IC2.5 (GND), IC2.PAD (GND), JP3.5, LED3.C, R4.2, R5.1, R6.1, R16.1, R19.2, R20.2, SJ1.2, VBAT0.1, VBAT0.NC1, VBAT0.NC2, X1.1, X2.A1B12 (GND), X2.B1A12 (GND)
ISET: IC2.8 (ISET), R1.1, R20.1
unnamed: R1.2, SJ1.1
unnamed: C6.1, D1.C, D2.C, IC2.10 (VBUS)
unnamed: CHG0.C, R12.2
unnamed: LED3.A, R10.1
unnamed: FAULT0.C, R13.2
STAT1: IC2.9 (STAT1), R13.1
STAT2: IC2.3 (STAT2), R12.1
SW: IC1.5 (SW), L1.2
THERM: IC2.6 (TS/MR), R16.2
V+: C7.1, CHG0.A, FAULT0.A, IC1.3 (VIN), IC2.1 (VSYS), L1.1, R2.1
VBAT: C8.1, IC2.2 (VBAT), JP3.6, VBAT0.2
VBUS: D2.A, JP3.2, X2.A4B9 (VBUS), X2.B4A9 (VBUS)
VIN: D1.A, JP3.1
VSET: IC2.7 (VSET), R19.1

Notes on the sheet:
WE 74438356010
